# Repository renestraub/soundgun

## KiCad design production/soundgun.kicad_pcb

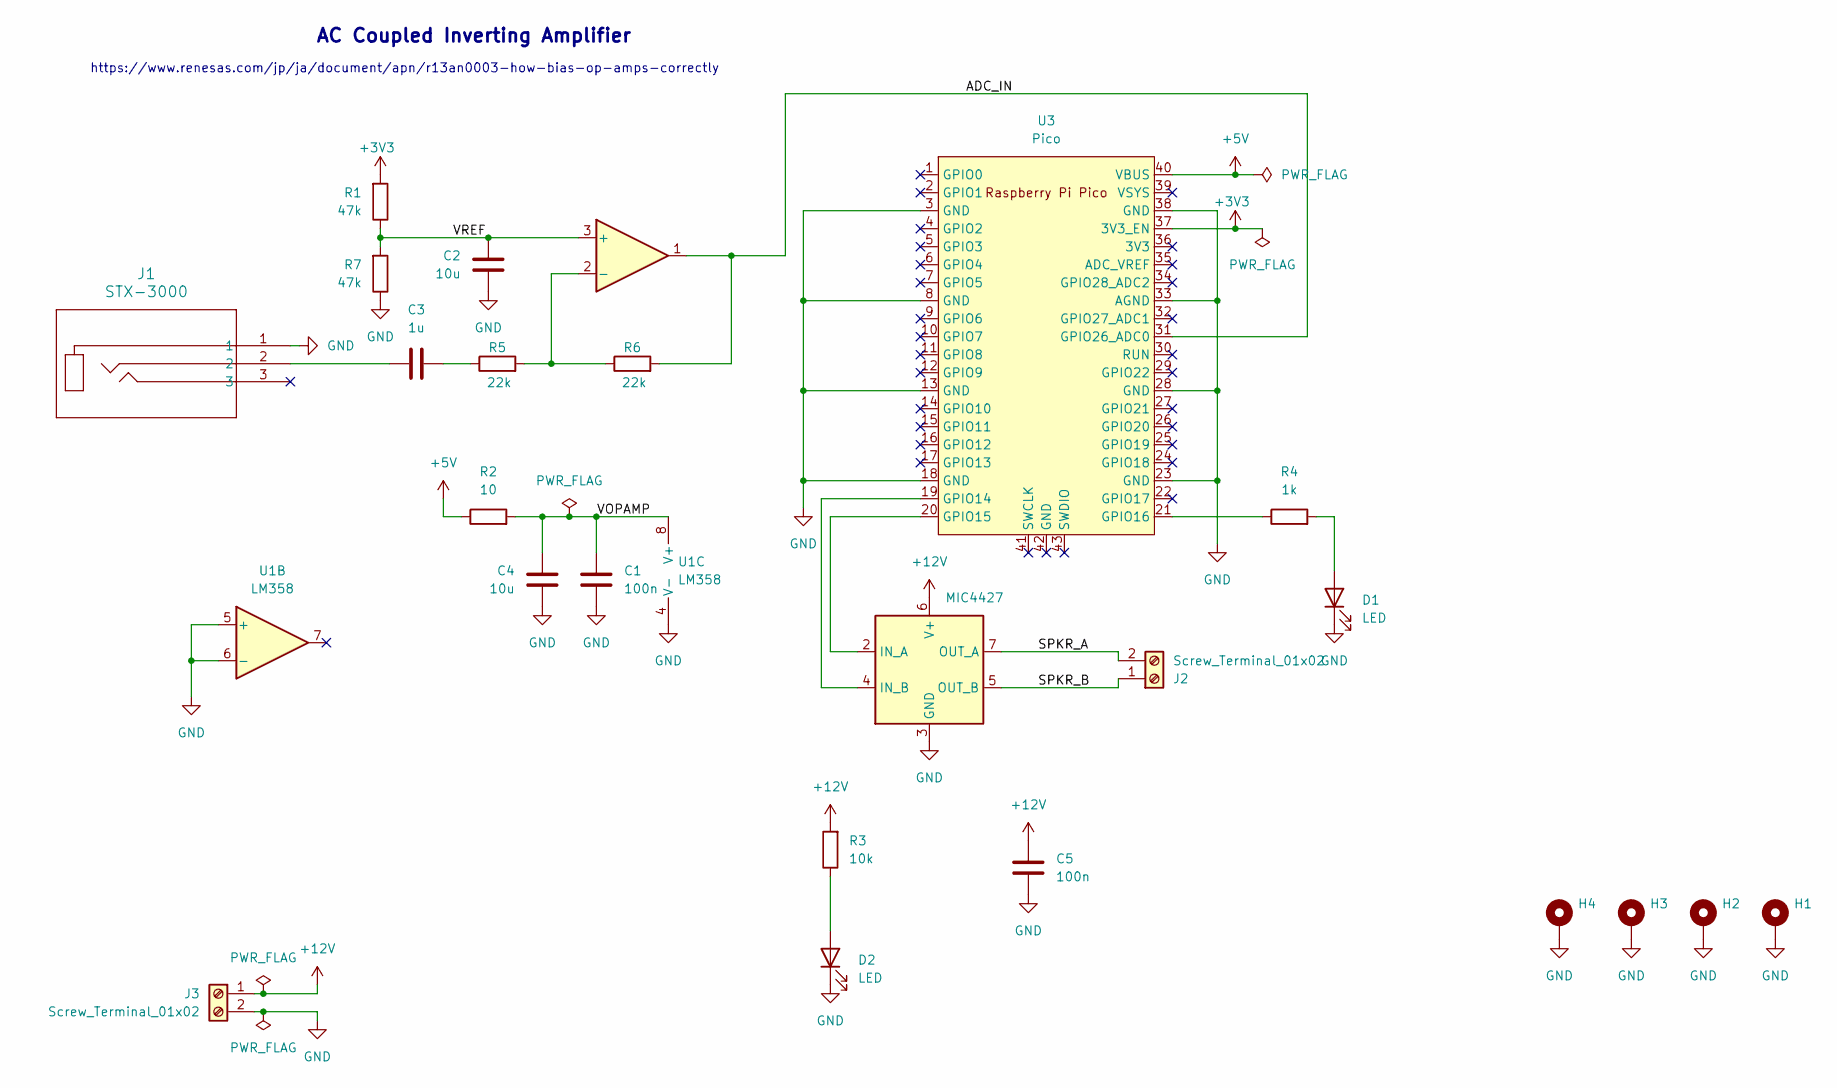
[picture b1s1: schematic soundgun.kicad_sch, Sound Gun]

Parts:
C1, C5: 100n; C_Disc_D3.8mm_W2.6mm_P2.50mm
C2, C4: 10u; C_Disc_D4.7mm_W2.5mm_P5.00mm
C3: 1u; C_Disc_D4.7mm_W2.5mm_P5.00mm
D1, D2: LED; LED_D5.0mm
H1, H2, H3, H4: MountingHole_Pad; MountingHole_3.2mm_M3_DIN965_Pad
J1: STX-3000; STX-3000_KYC
J2, J3: Screw_Terminal_01x02; TerminalBlock_Phoenix_PT-1,5-2-3.5-H_1x02_P3.50mm_Horizontal
R1, R7: 47k; R_Axial_DIN0204_L3.6mm_D1.6mm_P7.62mm_Horizontal
R2: 10; R_Axial_DIN0204_L3.6mm_D1.6mm_P7.62mm_Horizontal
R3: 10k; R_Axial_DIN0204_L3.6mm_D1.6mm_P7.62mm_Horizontal
R4: 1k; R_Axial_DIN0204_L3.6mm_D1.6mm_P7.62mm_Horizontal
R5, R6: 22k; R_Axial_DIN0204_L3.6mm_D1.6mm_P7.62mm_Horizontal
U1: LM358; DIP-8_W7.62mm_LongPads
U2: MIC4427; DIP-8_W7.62mm_LongPads
U3: Pico; RPi_Pico_SMD_TH

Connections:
+3V3: R1.2, U3.37 (3V3_EN)
+5V: R2.1, U3.40 (VBUS)
+12V: C5.2, J3.1, R3.2, U2.6 (V+)
/ADC_IN: R6.2, U1.1, U3.31 (GPIO26_ADC0)
/SPKR_A: J2.2, U2.7 (OUT_A)
/SPKR_B: J2.1, U2.5 (OUT_B)
/VOPAMP: C1.2, C4.2, R2.2, U1.8 (V+)
/VREF: C2.2, R1.1, R7.2, U1.3 (+)
GND: C1.1, C2.1, C4.1, C5.1, D1.1 (K), D2.1 (K), H1.1, H2.1, H3.1, H4.1, J1.1, J3.2, R7.1, U1.4 (V-), U1.5 (+), U1.6 (-), U2.3 (GND), U3.3 (GND), U3.8 (GND), U3.13 (GND), U3.18 (GND), U3.23 (GND), U3.28 (GND), U3.33 (AGND), U3.38 (GND)
unnamed: C3.1, J1.2
unnamed: C3.2, R5.1
unnamed: D1.2 (A), R4.2
unnamed: D2.2 (A), R3.1
unnamed: R5.2, R6.1, U1.2 (-)
unnamed: U2.2 (IN_A), U3.20 (GPIO15)
unnamed: U2.4 (IN_B), U3.19 (GPIO14)
unnamed: R4.1, U3.21 (GPIO16)

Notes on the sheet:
https://www.renesas.com/jp/ja/document/apn/r13an0003-how-bias-op-amps-correctly
AC Coupled Inverting Amplifier

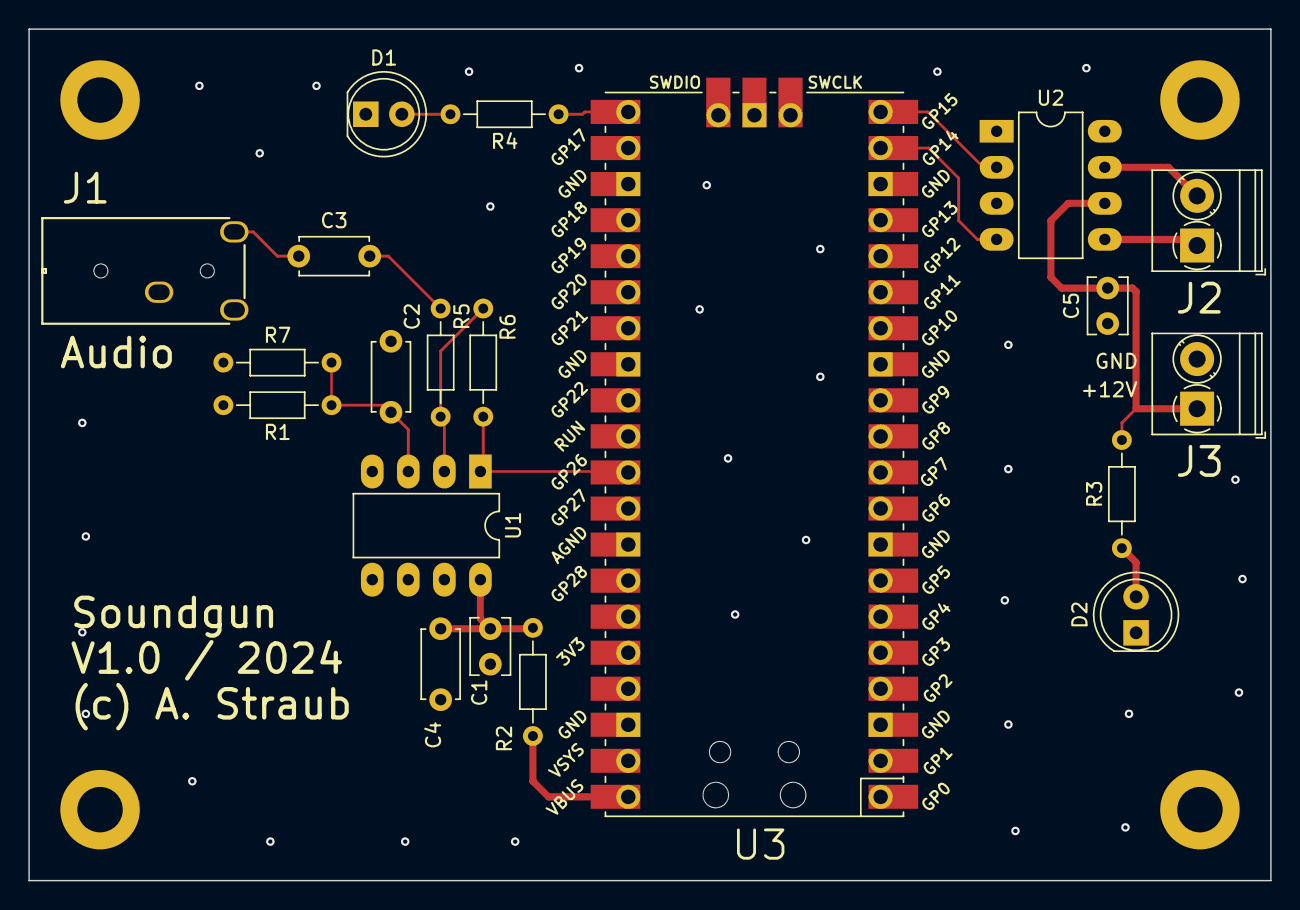
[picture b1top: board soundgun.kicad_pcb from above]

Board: 4 copper layers, 87.5 x 60.0 mm, 24 parts (0 on the bottom side), 17 nets.

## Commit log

2024-03-10 Rearranged files
2024-03-10 Updated gitignore
2024-03-10 Cleaned Release project
2024-03-10 Added libs
2024-03-10 Added model paths
2024-03-17 Created production PCB
2024-03-17 Created production data
2024-03-17 Keep ZIP archives away from repository
2024-04-11 Added original schematics image
2024-04-11 Added software to project
2024-04-16 Major refactoring
    - 40 kHz sampling rate, 12 bit samples
    - Machine code optimized
    - General cleanup
2024-04-16 Cleanup
2024-05-20 First release
    - Add LED toggling
    - Standalone run
